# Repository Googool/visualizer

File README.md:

# Visualizer 
Audio Spectrum Visualizer

### Documentation

### License

The content and software in this [repository](https://github.com/Googool/visualizer) are licensed under the [CC BY-SA 4.0](https://creativecommons.org/licenses/by-sa/4.0/?ref=chooser-v1).

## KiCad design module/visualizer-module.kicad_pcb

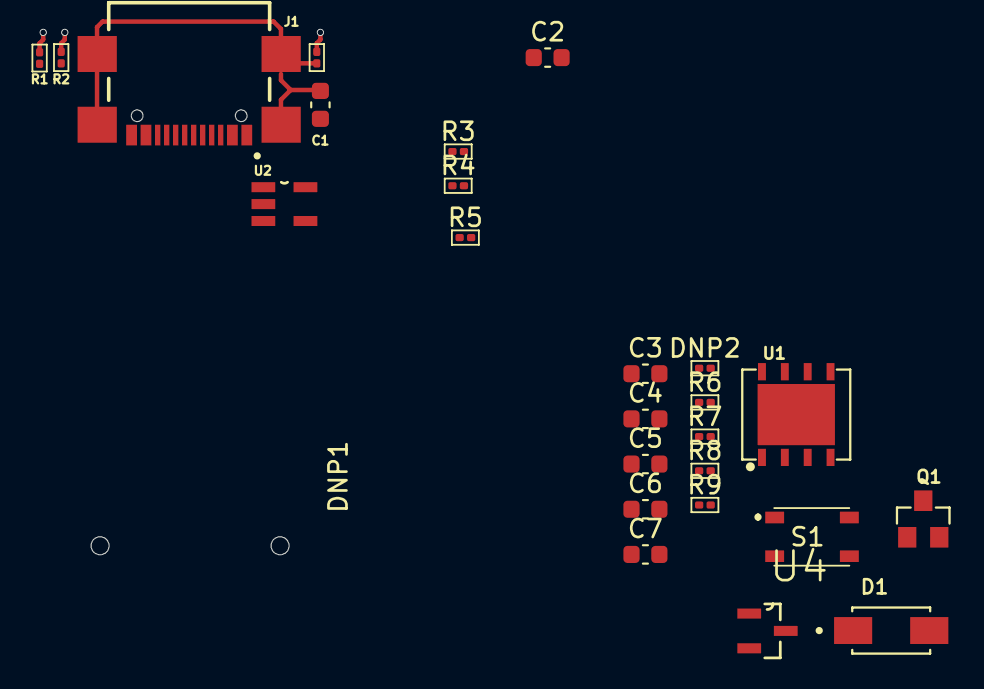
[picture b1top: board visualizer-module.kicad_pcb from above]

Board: 2 copper layers, 26 parts (1 on the bottom side), 16 nets.

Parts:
C1, C2, C3, C4, C5, C6, C7: 0.1uF_0603_16V; C_0603_1608Metric
D1: SS14
DISP1: SCREEN_1.47IN_172X320
DNP1, DNP2: 10K_0603; R_0201_0603Metric
J1: USB4110GFA
Q1: S8050
R1, R2, R4, R6, R7, R8, R9: 10K_0603; R_0201_0603Metric
R3: 1K_0603; R_0201_0603Metric
R5: 10R_0603; R_0201_0603Metric
S1: PTS810SJK250SMTRLFS; PTS810SJG250SMTRLFS
U1: W25Q128JVSIQ; W25Q128JVPIM
U2: SPX3819M5-L
U4: DMG3415U-7

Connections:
/3V3: C2.1, C3.1, C4.1, C5.1, DISP1.3 (LEDA), DISP1.4 (VDD), DNP2.1, R4.1, R7.2, U1.8 (VCC), U2.5 (VOUT)
/LEDK: DISP1.2 (LEDK), R5.2
/QSS: DNP2.2, R6.1, U1.1 (/CS)
/SH: C1.1, DNP1.2, J1.S1 (SHIELD), J1.S2 (SHIELD), J1.S3 (SHIELD), J1.S4 (SHIELD)
/USB_DN: J1.A6 (DP1), J1.B6 (DP2)
/USB_DP: J1.A7 (DN1), J1.B7 (DN2)
/VBUS: J1.A4/B9 (VBUS), J1.B4/A9 (VBUS), U4.3
/VIN: C6.1, C7.1, U2.1 (VIN), U2.3 (EN), U4.2
/VSYS: R9.2, U4.1
GND: C1.2, C2.2, C3.2, C4.2, C5.2, C6.2, C7.2, DISP1.1 (GND), DISP1.5 (GND), DISP1.6 (GND), DISP1.12 (GND), DNP1.1, J1.A1/B12 (GND), J1.B1/A12 (GND), Q1.1, R1.1, R2.1, R8.1, R9.1, S1.1, S1.2, U1.4 (GND), U2.2 (GND)
unnamed: J1.A5 (CC1), R1.2
unnamed: J1.B5 (CC2), R2.2
unnamed: Q1.2, R3.2, R4.2
unnamed: Q1.3, R5.1
unnamed: R6.2, S1.3, S1.4
unnamed: R7.1, R8.2, U2.4 (ADJ/BYP)

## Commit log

2024-02-15 Create LICENSE
2024-02-19 Boom?
2024-02-19 Does this work?
2024-02-19 Fix?
2024-02-19 This?
2024-02-19 Resize
2024-02-19 Editing the symbols, schematic and other stuff
2024-02-19 Ignoring fp-info-cache within module folder
2024-02-20 Added more components and edited schematic
2024-02-20 Added an additional datasheet for the RP2040
2024-02-20 Added and edited some components + schematic update
2024-02-20 kicad_sch.lck added to .gitignore
2024-02-20 Trying to create a MicroPython project within the repository
2024-02-20 Removed the MicroPython files
2024-02-20 Updated symbol and attached some models to some of the components
